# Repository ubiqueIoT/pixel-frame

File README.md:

# Pixel Frame

The pixel frame is a 240 x 240px desktop display platform. This repository contains all of the hardware and software files needed to build this project. 

Most of the components can be sourced from Adafruit:

| Item | Link |
|------|------|
| M2.5 x 12mm M-F hex nylon standoff | https://www.aliexpress.com/item/2251832604652301.html?spm=a2g0o.order_list.0.0.65d3180220YNC3 |
| Heat set insterts (M2.5 x 4.0 x 3.6) | https://www.aliexpress.com/item/3256801886329635.html?spm=a2g0o.order_list.0.0.65d3180220YNC3 |
| M2.5 x 10mm nylon screw | https://www.aliexpress.com/item/3256802895548825.html?spm=a2g0o.order_detail.0.0.485df19cqwiPWp |
| 1.54" TFT LCD display | https://www.adafruit.com/product/3787 |
| M4 Express ItsyBitsy board | https://www.adafruit.com/product/3800 |
| Case | 3D Printed (SLA) |
| Adapter PCB | Custom |

## 3D Printed Case:

## Adapter PCB:

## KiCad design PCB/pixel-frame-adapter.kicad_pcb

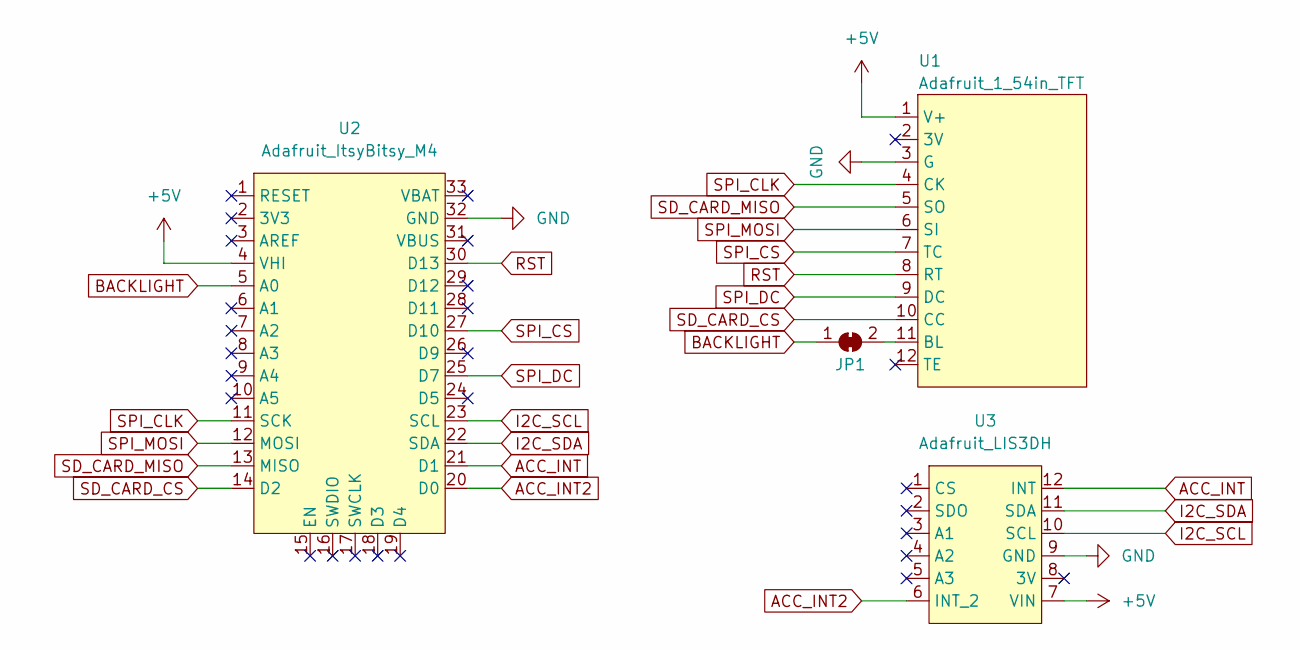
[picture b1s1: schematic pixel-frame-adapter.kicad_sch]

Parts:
JP1: SolderJumper_2_Bridged; SolderJumper-2_P1.3mm_Bridged_RoundedPad1.0x1.5mm
U1: Adafruit_1_54in_TFT; Adafruit_2_54in_TFT_Display
U2: Adafruit_ItsyBitsy_M4
U3: Adafruit_LIS3DH

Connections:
+5V: U1.1 (V+), U2.4 (VHI), U3.7 (VIN)
ACC_INT: U2.21 (D1), U3.12 (INT)
ACC_INT2: U2.20 (D0), U3.6 (INT_2)
BACKLIGHT: JP1.1 (A), U2.5 (A0)
GND: U1.3 (G), U2.32 (GND), U3.9 (GND)
I2C_SCL: U2.23 (SCL), U3.10 (SCL)
I2C_SDA: U2.22 (SDA), U3.11 (SDA)
unnamed: JP1.2 (B), U1.11 (BL)
RST: U1.8 (RT), U2.30 (D13)
SD_CARD_CS: U1.10 (CC), U2.14 (D2)
SD_CARD_MISO: U1.5 (SO), U2.13 (MISO)
SPI_CLK: U1.4 (CK), U2.11 (SCK)
SPI_CS: U1.7 (TC), U2.27 (D10)
SPI_DC: U1.9 (DC), U2.25 (D7)
SPI_MOSI: U1.6 (SI), U2.12 (MOSI)

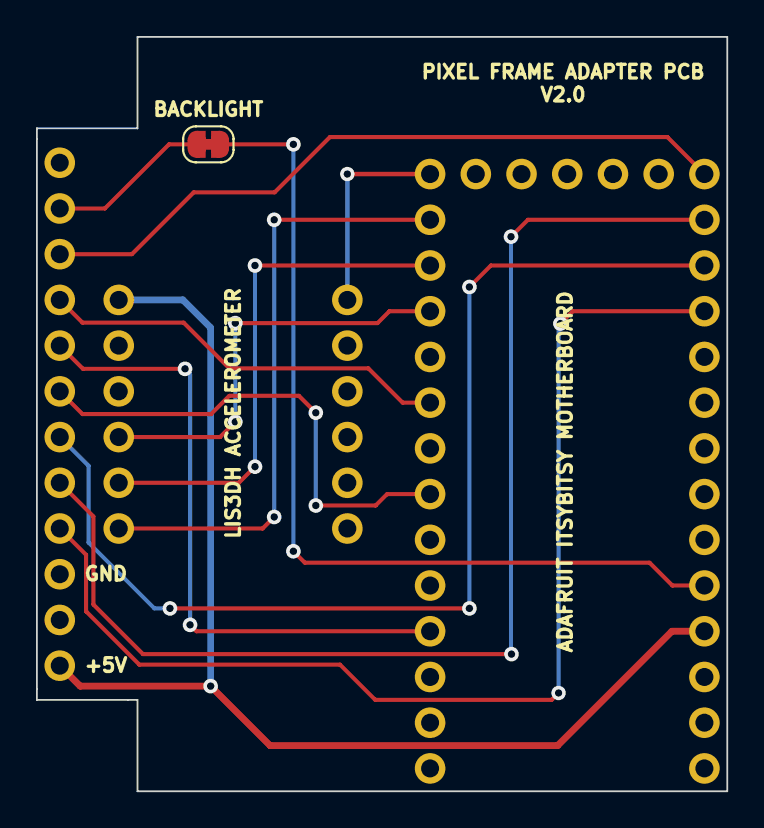
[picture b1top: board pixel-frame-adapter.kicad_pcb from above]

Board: 2 copper layers, 38.4 x 41.9 mm, 4 parts (0 on the bottom side), 15 nets.

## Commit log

2022-07-20 file clean up
2022-07-20 git ignore
2022-08-01 rev-1
2022-08-01 rotate USB port
2022-08-01 line up usb
2022-08-03 routing done
2022-08-03 new gitignore
2022-08-03 rename file
2022-08-03 small re-route
2022-08-04 dimensions and track cleanup
2022-08-04 silkscreen
2022-08-04 clean up
2022-08-04 even numbers
2022-08-22 handle through hole tolerances
2022-09-14 updated CAD
2022-09-14 update gerbers
